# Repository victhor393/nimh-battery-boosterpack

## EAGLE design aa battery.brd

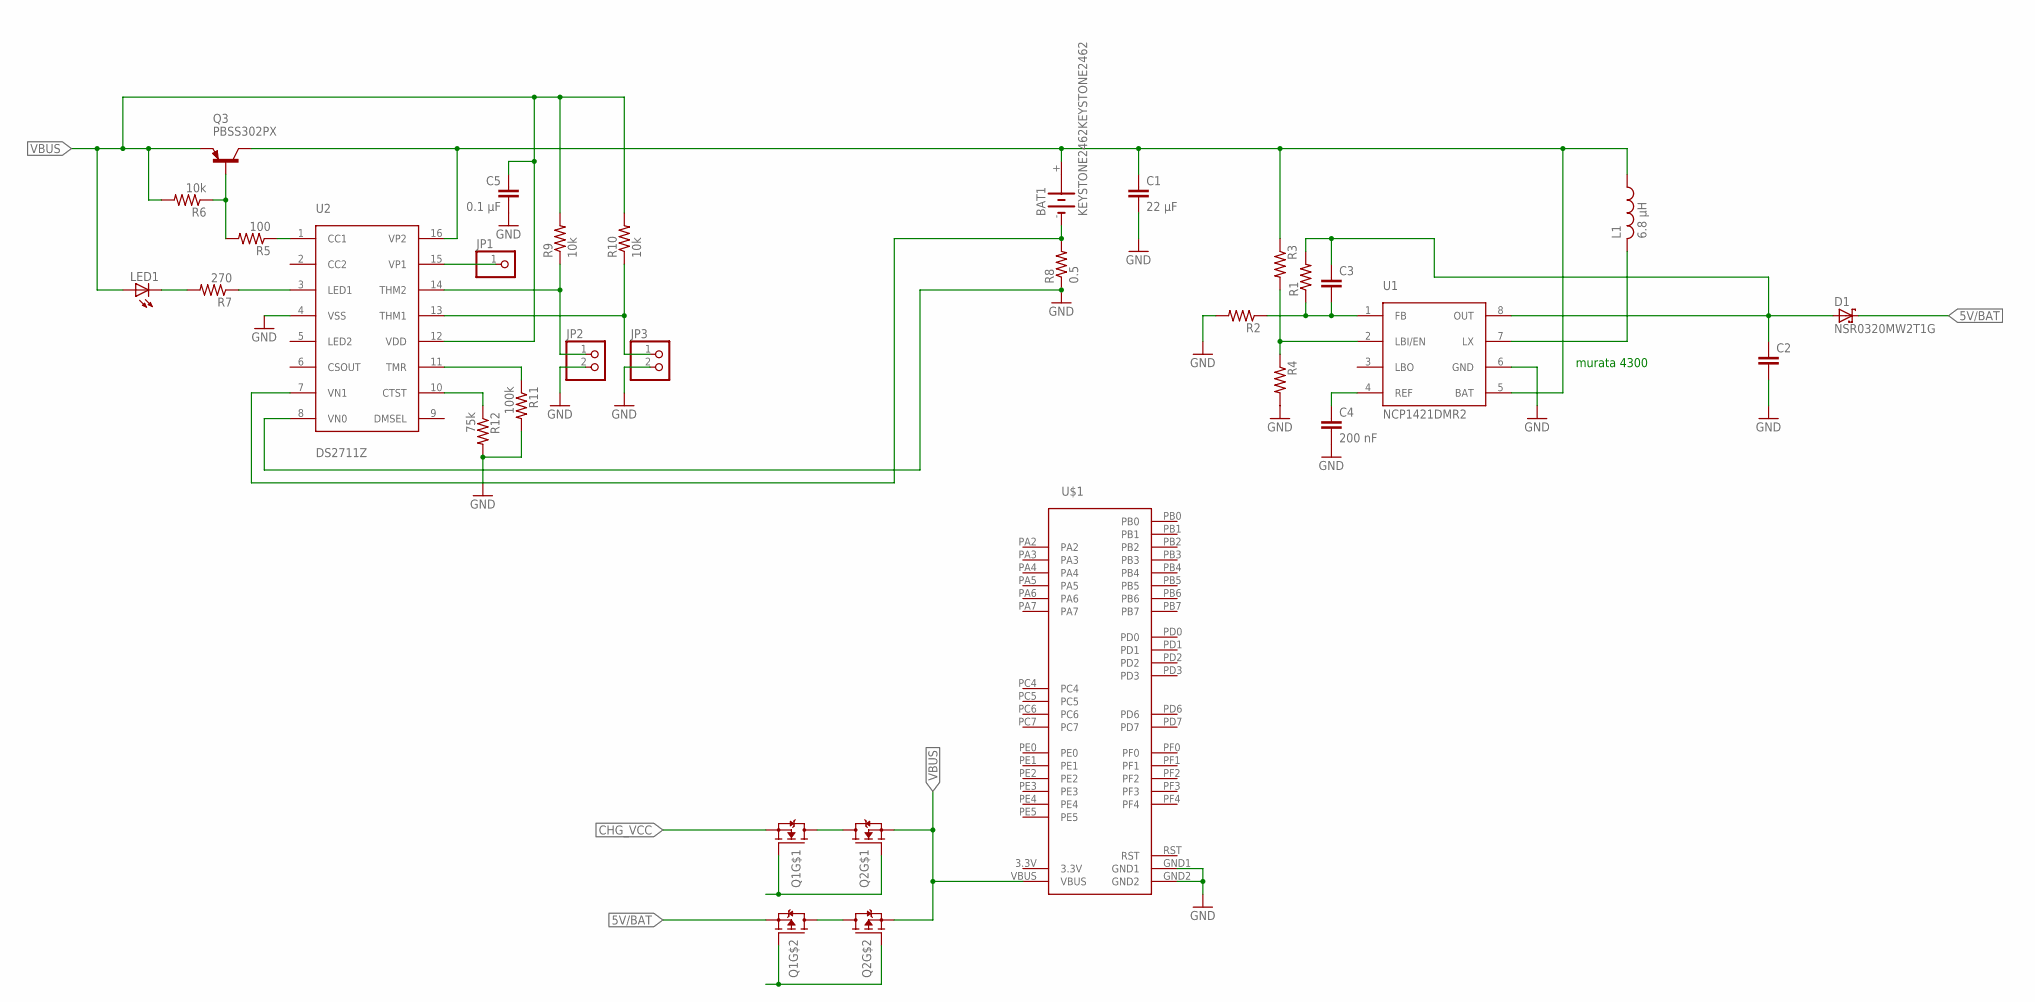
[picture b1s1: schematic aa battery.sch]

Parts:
BAT1: KEYSTONE2462KEYSTONE2462; KEYSTONE2462
C1: 22 µF; C0805
C2: C-EUC1210; C1210
C3: C-EUC0805; C0805
C4: 200 nF; C0805
C5: 0.1 µF; C0805
D1: NSR0320MW2T1G; SOD323
JP1: PINHD-1X1; 1X01
JP2, JP3: PINHD-1X2; 1X02
L1: 6.8 µH; MURATA4500
LED1: LED5MM
Q1, Q2: DMC2038LVT-7; TSOT26
Q3: PBSS302PX; SOT89-BCE
R1, R2, R3, R4: R-US_R0805; R0805
R5: 100; R0805
R6, R9, R10: 10k; R0805
R7: 270; R0805
R8: 0.5; R0805
R11: 100k; R0805
R12: 75k; R0805
U1: NCP1421DMR2; MICRO8
U2: DS2711Z; SO16
U$1: STELLARIS-LAUNCHPADSTELLARIS-LAUNCHPAD-XL; LAUNCHPAD-XL

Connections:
3.3V: U$1.3.3V
5V/BAT: D1.C, Q1.2 (S1)
CHG_VCC: Q1.5 (S)
GND: C1.2, C2.2, C4.2, C5.2, JP2.2, JP3.2, R2.2, R4.2, R8.1, R11.2, R12.2, U1.6 (GND), U2.4 (VSS), U2.8 (VN0), U$1.GND1, U$1.GND2
unnamed: C4.1, U1.4 (REF)
unnamed: L1.2, U1.7 (LX)
unnamed: C3.2, R1.1, R2.1, U1.1 (FB)
unnamed: Q1.4 (D1), Q2.4 (D1)
unnamed: R3.2, R4.1, U1.2 (LBI/EN)
unnamed: BAT1.+, C1.1, L1.1, Q3.C, Q3.C@1 (C), R3.1, U1.5 (BAT), U2.16 (VP2)
unnamed: Q3.B, R5.2, R6.1
unnamed: Q1.6 (D), Q2.6 (D)
unnamed: Q1.1 (G), Q2.1 (G)
unnamed: R5.1, U2.1 (CC1)
unnamed: C2.1, C3.1, D1.A, R1.2, U1.8 (OUT)
unnamed: Q1.3 (G1), Q2.3 (G1)
unnamed: JP1.1, U2.15 (VP1)
unnamed: BAT1.-, R8.2, U2.7 (VN1)
unnamed: LED1.K (C), R7.2
unnamed: R7.1, U2.3 (LED1)
unnamed: JP2.1, R9.1, U2.14 (THM2)
unnamed: JP3.1, R10.1, U2.13 (THM1)
unnamed: R12.1, U2.10 (CTST)
unnamed: R11.1, U2.11 (TMR)
RST: U$1.RST
VBUS: C5.1, LED1.A, Q2.2 (S1), Q2.5 (S), Q3.E, R6.2, R9.2, R10.2, U2.12 (VDD), U$1.VBUS

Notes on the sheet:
murata 4300

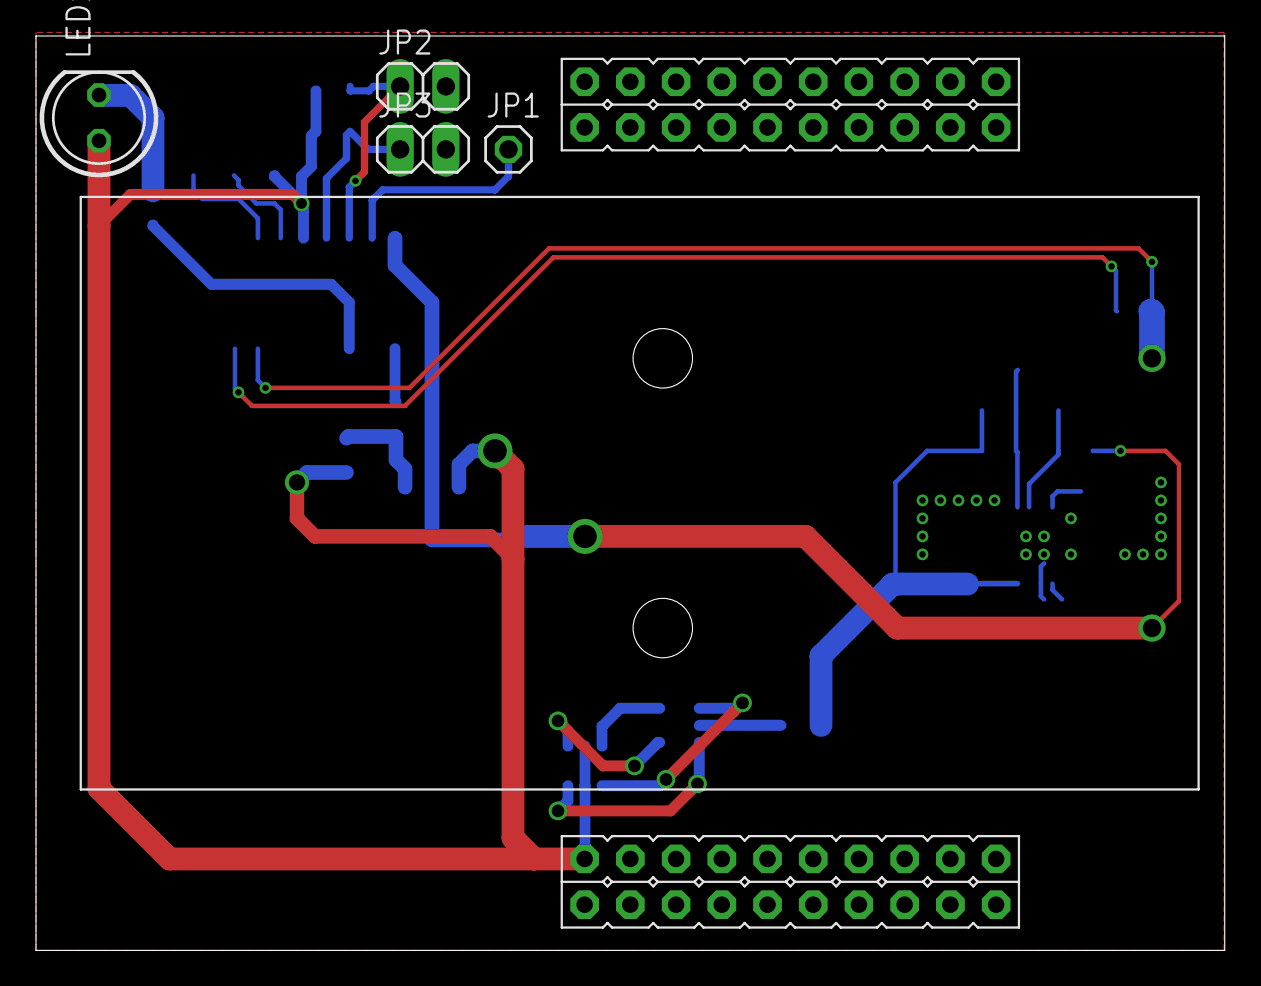
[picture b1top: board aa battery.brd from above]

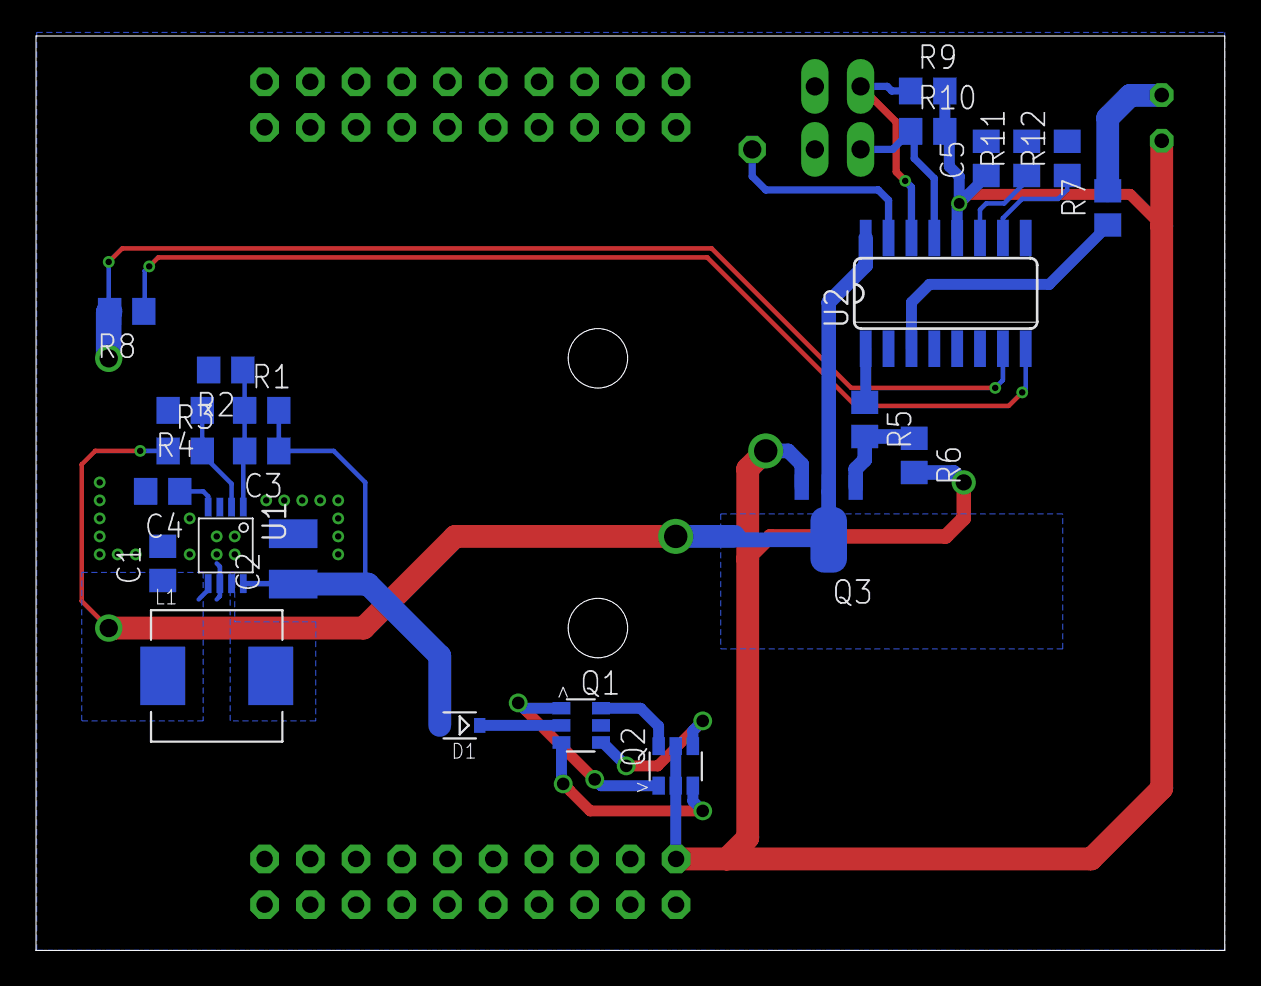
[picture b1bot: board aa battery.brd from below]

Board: 2 copper layers, 66.0 x 50.8 mm, 30 parts (24 on the bottom side), 23 nets.

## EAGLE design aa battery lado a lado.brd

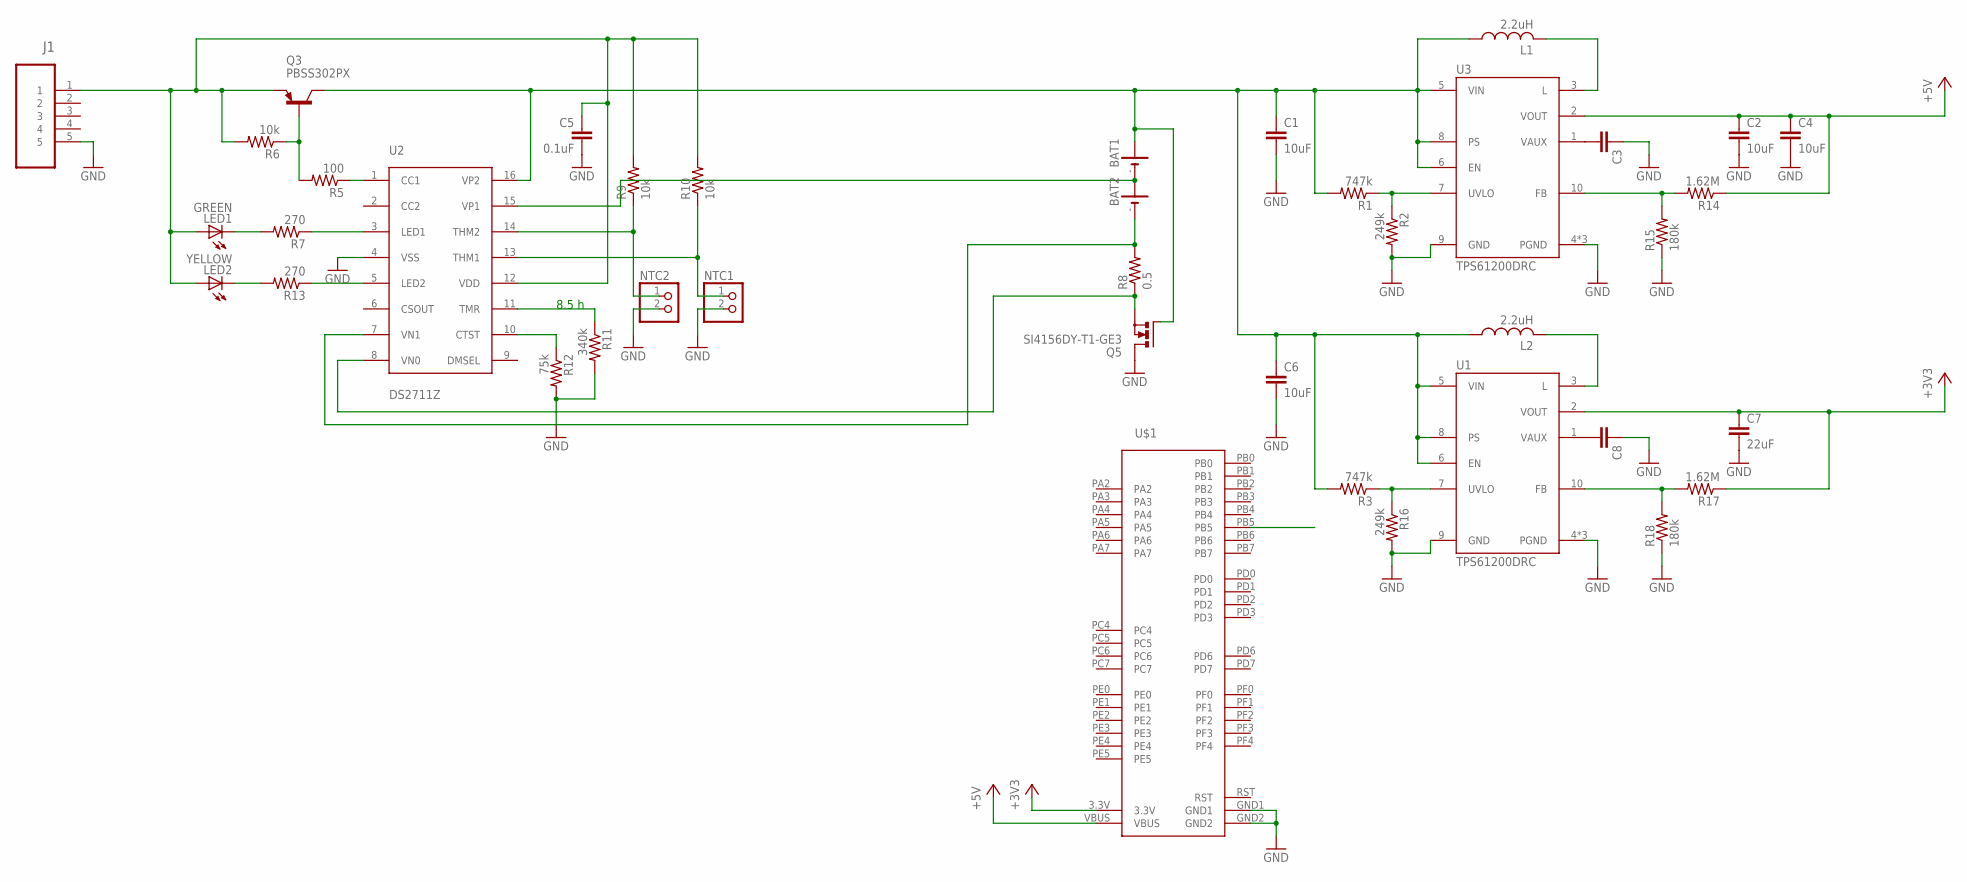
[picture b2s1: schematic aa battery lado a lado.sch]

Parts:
BAT1, BAT2: AA-SNGLKEYSTONE2460; KEYSTONE2460
C1, C2, C4, C6: 10uF; C0805
C3: C-EUC0805; C0805
C5: 0.1uF; C0805
C7: 22uF; C0805
C8: C-EUC0603; C0603
J1: 47346-0001; MOLEX_47346-0001
L1, L2: 2.2uH; XAL4040
LED1: GREEN; SML1206
LED2: YELLOW; SML1206
NTC1, NTC2: PINHD-1X2; 1X02
Q3: PBSS302PX; SOT89-BCE
Q5: SI4156DY-T1-GE3; SO-08
R1, R3: 747k; R0603
R2, R16: 249k; R0603
R5: 100; R0805
R6, R9, R10: 10k; R0805
R7, R13: 270; R0805
R8: 0.5; R0805
R11: 340k; R0805
R12: 75k; R0805
R14, R17: 1.62M; R0603
R15, R18: 180k; R0603
U1, U3: TPS61200DRC; DRC10_2P4X1P65
U2: DS2711Z; SO16
U$1: STELLARIS-LAUNCHPADSTELLARIS-LAUNCHPAD-XL-HALF-LE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; LAUNCHPAD-XL-HALF-LENGTH

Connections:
+3V3: C7.1, R17.1, U1.2 (VOUT), U$1.3.3V
+5V: C2.1, C4.1, R14.1, U3.2 (VOUT), U$1.VBUS
CHG_VCC: C5.1, J1.1, LED1.A, LED2.A, Q3.E, R6.2, R9.2, R10.2, U2.12 (VDD)
GND: C1.2, C2.2, C3.1, C4.2, C5.2, C6.2, C7.2, C8.1, J1.5, NTC1.2, NTC2.2, Q5.5 (D), Q5.6 (D), Q5.7 (D), Q5.8 (D), R2.2, R11.2, R12.2, R15.1, R16.2, R18.1, U1.4 (PGND), U1.9 (GND), U1.11 (PGND), U1.12 (PGND), U2.4 (VSS), U3.4 (PGND), U3.9 (GND), U3.11 (PGND), U3.12 (PGND), U$1.GND1, U$1.GND2
unnamed: BAT1.+, C1.1, C6.1, L1.1, L2.1, Q3.C, Q3.C@1 (C), Q5.4 (G), R1.2, R3.2, U1.5 (VIN), U1.6 (EN), U1.8 (PS), U2.16 (VP2), U3.5 (VIN), U3.6 (EN), U3.8 (PS)
unnamed: L2.2, U1.3 (L)
unnamed: R1.1, R2.1, U3.7 (UVLO)
unnamed: C3.2, U3.1 (VAUX)
unnamed: R14.2, R15.2, U3.10 (FB)
unnamed: R3.1, R16.1, U1.7 (UVLO)
unnamed: Q3.B, R5.2, R6.1
unnamed: L1.2, U3.3 (L)
unnamed: C8.2, U1.1 (VAUX)
unnamed: R5.1, U2.1 (CC1)
unnamed: R17.2, R18.2, U1.10 (FB)
unnamed: BAT1.-, BAT2.+, U2.15 (VP1)
unnamed: BAT2.-, R8.2, U2.7 (VN1)
unnamed: LED1.C, R7.2
unnamed: R7.1, U2.3 (LED1)
unnamed: NTC2.1, R9.1, U2.14 (THM2)
unnamed: NTC1.1, R10.1, U2.13 (THM1)
unnamed: R13.1, U2.5 (LED2)
unnamed: R12.1, U2.10 (CTST)
unnamed: R11.1, U2.11 (TMR)
unnamed: LED2.C, R13.2
unnamed: Q5.1 (S), Q5.2 (S), Q5.3 (S), R8.1, U2.8 (VN0)
RST: U$1.RST

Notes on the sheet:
8.5 h

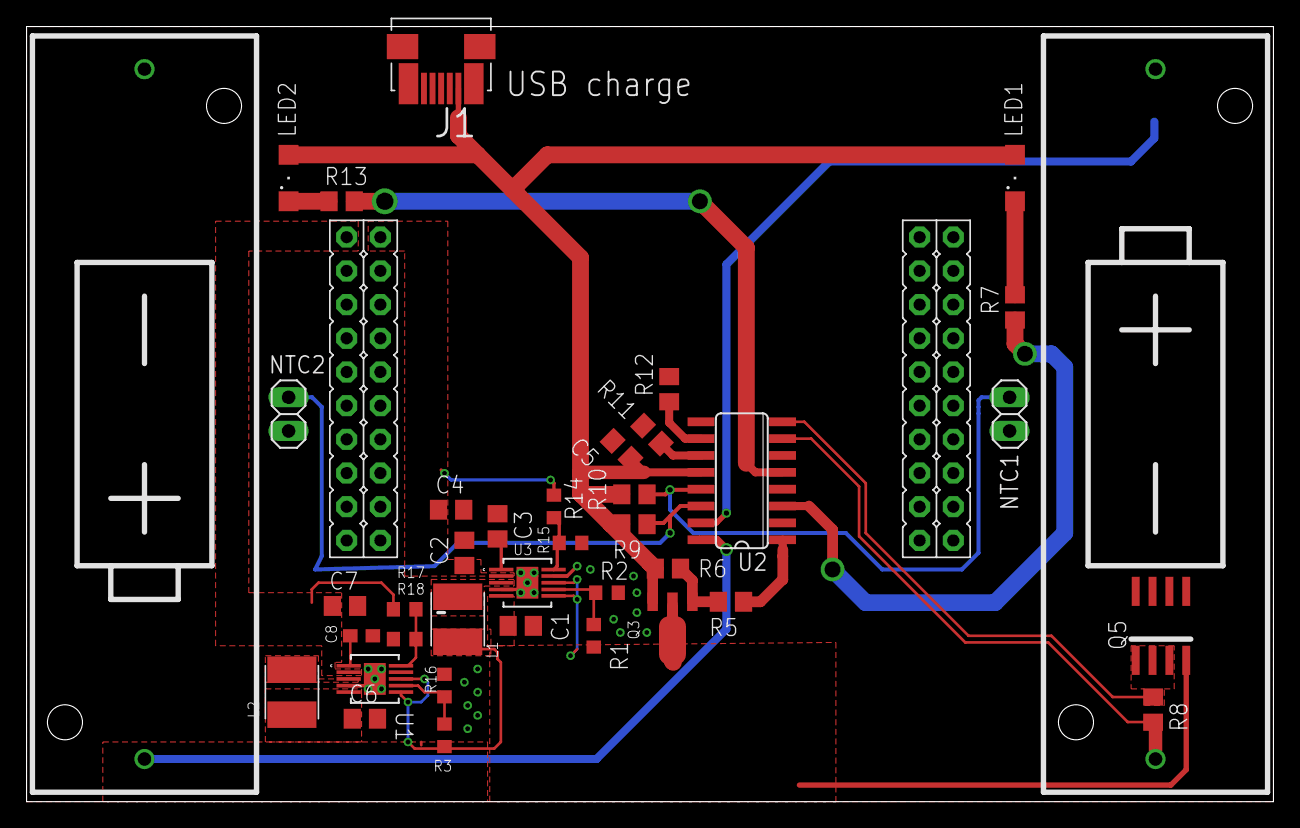
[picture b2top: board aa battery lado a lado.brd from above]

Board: 2 copper layers, 94.0 x 58.4 mm, 40 parts (0 on the bottom side), 26 nets.

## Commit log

2019-05-12 Initial commit fix
2019-05-21 Added schematic and board layout in pdf format
